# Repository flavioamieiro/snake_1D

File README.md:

A snake trapped in one dimension.

It's always there, but you'll need a strip of ws2812b LEDs to see and interact with it.

Here, you'll find two species: The [python](fadecandy_python/#readme),
for which you'll need a computer and a
[fadecandy](https://github.com/scanlime/fadecandy) and the
[tiny](attiny85_arduino_IDE/#readme), for which you can use the
standalone [hardware](hardware/#readme).

The software in this repository is licensed under the GPLv3 and the hardware
under the CERN-OHL-S v2.

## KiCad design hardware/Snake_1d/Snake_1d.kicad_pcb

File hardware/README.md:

Kicad project with schematics and PCB design for the 1D Snake Game
running on an ATTiny85.

This source describes Open Hardware and is licensed under the
CERN-OHL-S v2.  You may redistribute and modify this source and make
products using it under the terms of the CERN-OHL-S v2
(https://ohwr.org/cern_ohl_s_v2.txt).

This source is distributed WITHOUT ANY EXPRESS OR IMPLIED WARRANTY,
INCLUDING OF MERCHANTABILITY, SATISFACTORY QUALITY AND FITNESS FOR A
PARTICULAR PURPOSE. Please see the CERN-OHL-S v2 for applicable
conditions.

Source location:
https://github.com/flavioamieiro/snake_1D

As per CERN-OHL-S v2 section 4, should You produce hardware based on
this source, You must where practicable maintain the Source Location
visible on the external case of the Gizmo or other products you make
using this source.

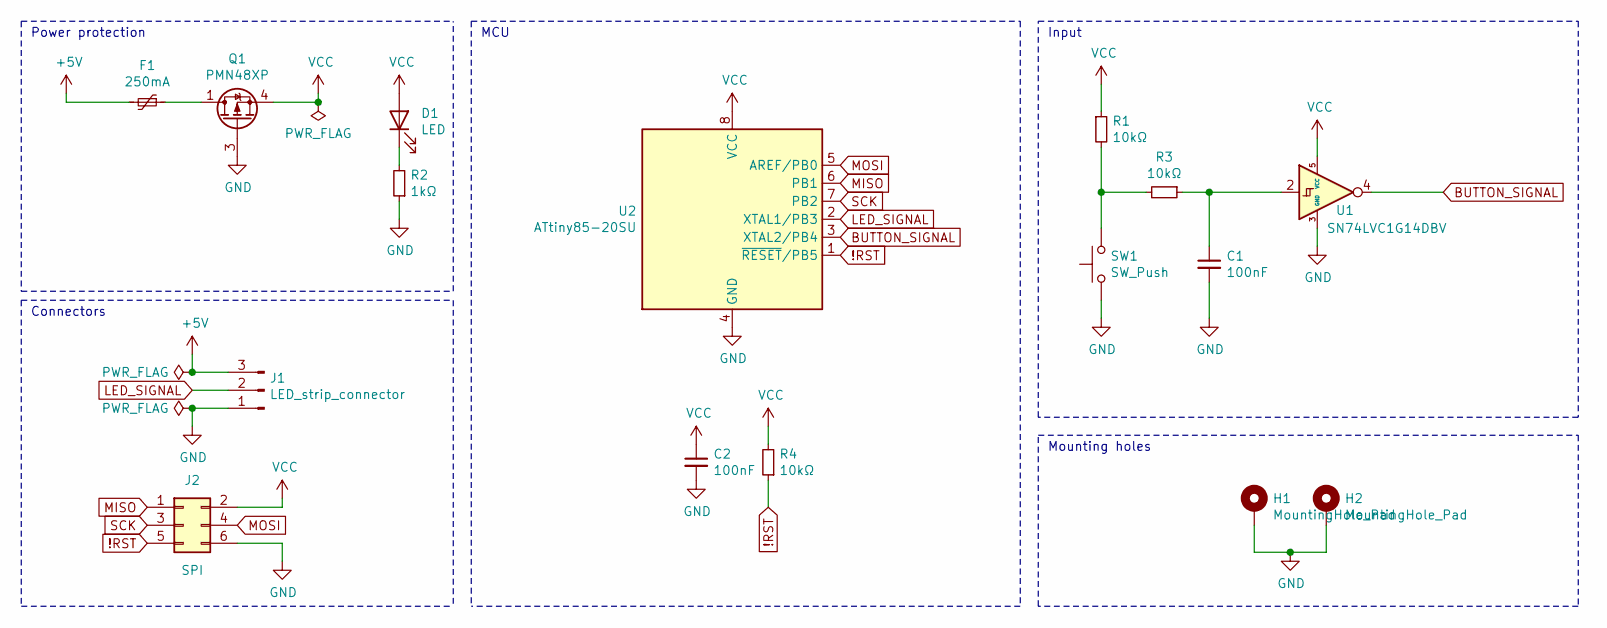
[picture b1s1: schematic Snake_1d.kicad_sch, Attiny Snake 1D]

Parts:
C1, C2: 100nF; C_1206_3216Metric_Pad1.33x1.80mm_HandSolder
D1: LED; LED_1206_3216Metric_Pad1.42x1.75mm_HandSolder
F1: 250mA; Fuse_1206_3216Metric_Pad1.42x1.75mm_HandSolder
H1, H2: MountingHole_Pad; MountingHole_3.2mm_M3_Pad_Via
J1: LED_strip_connector; PinHeader_1x03_P2.54mm_Horizontal
J2: SPI; SPI_pads_2.54mm
Q1: PMN48XP; TSOP-6_1.65x3.05mm_P0.95mm
R1, R3, R4: 10kΩ; R_0805_2012Metric_Pad1.20x1.40mm_HandSolder
R2: 1kΩ; R_1206_3216Metric_Pad1.30x1.75mm_HandSolder
SW1: SW_Push; SW_Cherry_MX_1.00u_PCB
U1: SN74LVC1G14DBV; SOT-23-5_HandSoldering
U2: ATtiny85-20SU; SOIJ-8_5.3x5.3mm_P1.27mm

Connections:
!RST: J2.5, R4.1, U2.1 (~RESET~/PB5)
+5V: F1.2, J1.3
BUTTON_SIGNAL: U1.4, U2.3 (XTAL2/PB4)
GND: C1.2, C2.2, H1.1, H2.1, J1.1, J2.6, Q1.3 (G), R2.1, SW1.1, U1.3 (GND), U2.4 (GND)
LED_SIGNAL: J1.2, U2.2 (XTAL1/PB3)
MISO: J2.1, U2.6 (PB1)
MOSI: J2.4, U2.5 (AREF/PB0)
unnamed: C1.1, R3.1, U1.2
unnamed: D1.1 (K), R2.2
unnamed: F1.1, Q1.1 (D), Q1.2 (D), Q1.5 (D), Q1.6 (D)
unnamed: R1.2, R3.2, SW1.2
SCK: J2.3, U2.7 (PB2)
VCC: C2.1, D1.2 (A), J2.2, Q1.4 (S), R1.1, R4.2, U1.5 (VCC), U2.8 (VCC)

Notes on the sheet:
Power protection
Connectors
MCU
Input
Mounting holes

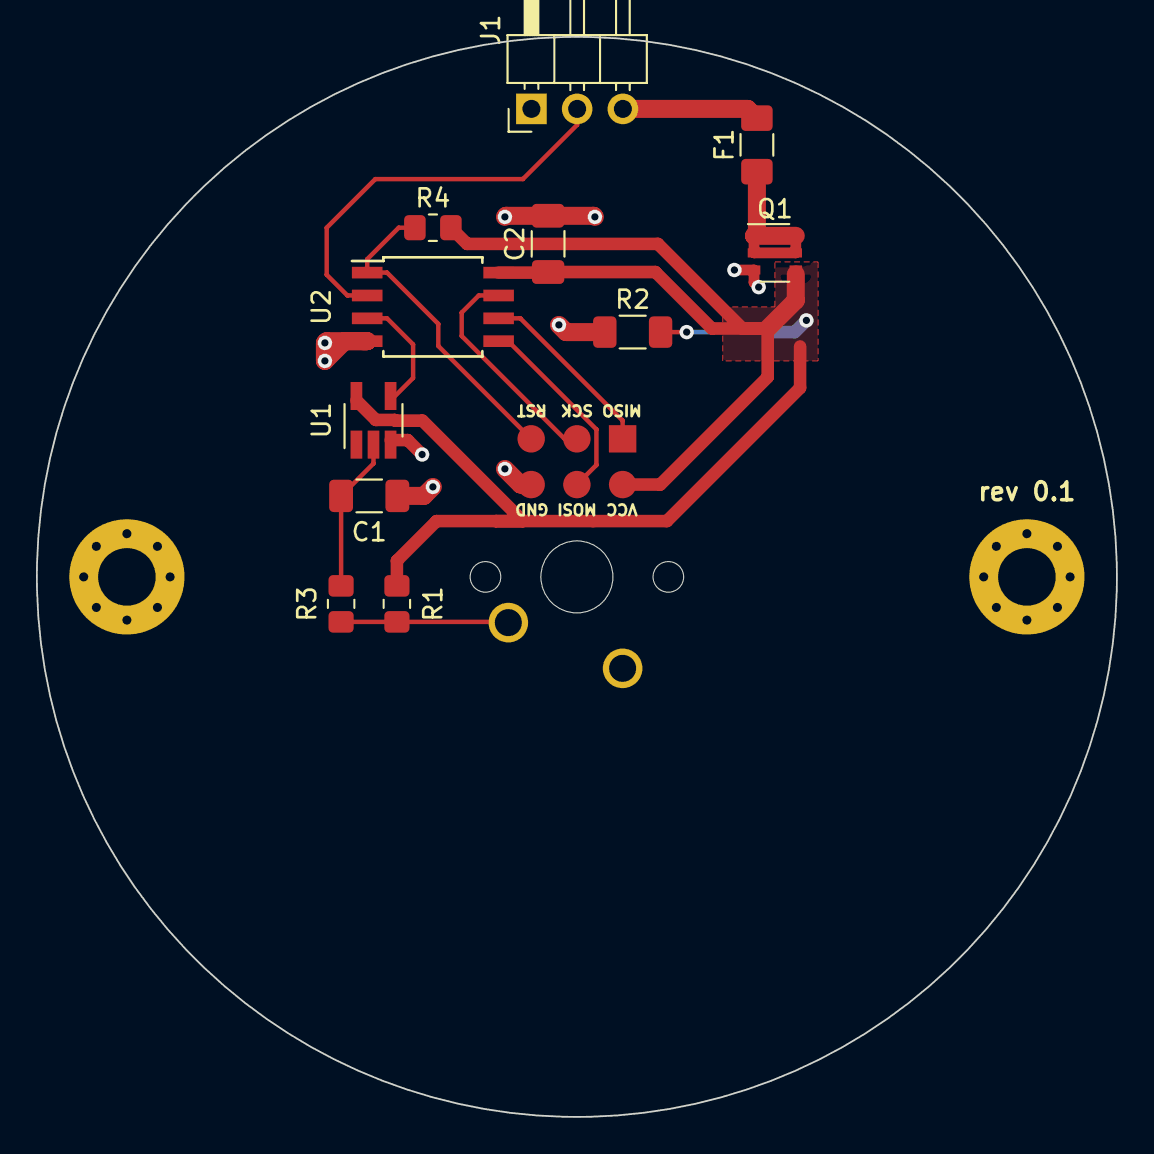
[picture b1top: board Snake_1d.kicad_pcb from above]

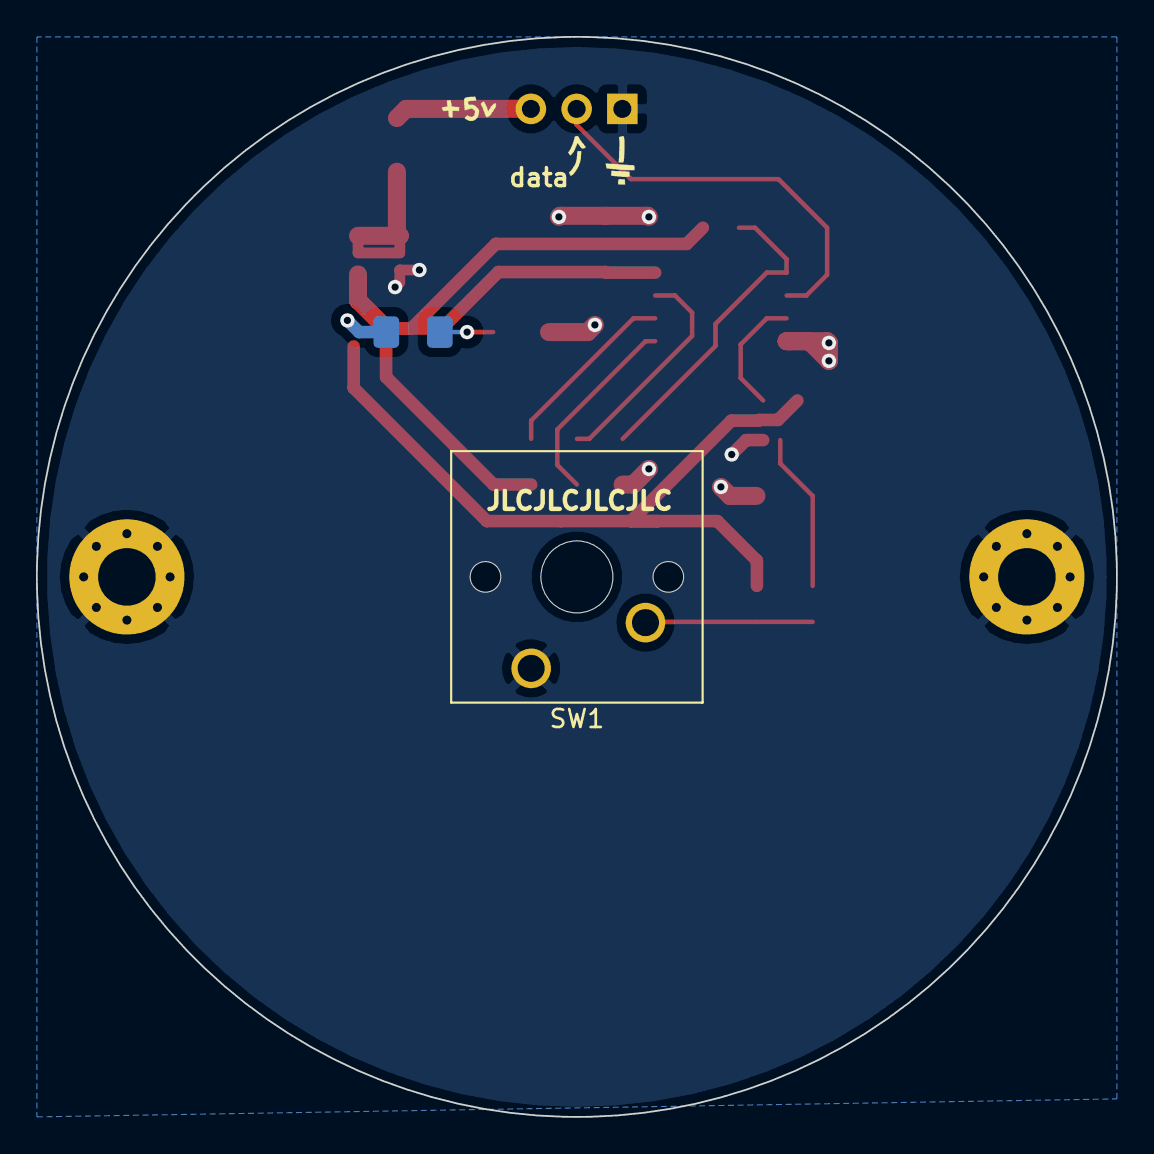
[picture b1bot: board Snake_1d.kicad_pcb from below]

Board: 2 copper layers, 60.0 x 60.0 mm, 19 parts (5 on the bottom side), 13 nets.

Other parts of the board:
Ref**: Val**; 5v_FSilks
Ref**#2: Val**; arrow_up_from_left
Ref**#3: Val**; ground_FSilks

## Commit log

2020-10-05 Adds README.html to .gitignore
    Emacs mode's live preview generates temporary html files.
2020-10-05 Adds Fadecandy/Python implementation
    The code was basically copied from [an earlier
    implementation](https://github.com/flavioamieiro/snake_game) (minus
    tests) and adapted to use fadecandy to interface with the ws2812b LED
    strip.
2020-10-05 Adds ATTiny85 version of the game
    It's still buggy and doesn't run as smooth as the python version, but
    it runs without a computer and a USB connection.
2020-10-05 Changes the license of the python implementation to GPLv3
    Even though the [original
    implementation](https://github.com/flavioamieiro/snake_game) uses
    GPLv2 without the "any later version" option, I am the copyright owner
    and can change it.
2020-10-05 Adds kicad project with hardware schematics
    It also includes the custom footprint for the programming port.
2020-10-05 Adds top-level README file
2020-10-05 Adds courtyard area to SPI pads footprint
2020-10-05 Adds mounting holes to the schematic
2020-10-06 Adds PCB layout
    The components are laid out and the tracks are routed, but I still need
    to improve the silkscreen and general look and feel.
2020-10-09 Moves LED via a bit away from the main Vcc rail
2020-10-09 Organizes silkscreen on the pcb
2020-10-09 Adds pcb file changes after generating Gerber files
2020-10-09 Adds revision number to silkscreen on pcb
2020-10-09 Adds pin 1 marks to ICs on the PCB
2020-10-09 Adds silkscreen labels to programming connector on PCB
2020-10-09 Adds JLC order number placeholder to pcb
2020-12-16 Moves connector label to the front side of the PCB
2020-12-16 Changes cherry switch to PCB mount
2020-12-16 Changes footprints to handsolder where possible
2020-12-16 Increases silk size for programming connector
2020-12-16 Fixes missing (silk) footprints
2021-02-10 Moves kicad files to new (nightly) format
2021-03-12 Changes LED strip connector footprint to horizontal pin header
2021-03-12 Adds Freecad project with the model of an enclosure for 3D printing
2021-03-30 Updates kicad file version
2021-03-30 Adds license information for the hardware
